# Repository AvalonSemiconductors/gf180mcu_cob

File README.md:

# gf180mcu_cob
Experimenting with Chip On Board setups for GF180MCU chips, most importantly gf180 Caravel.

Currently contains Pad-out diagrams and KiCad footprints for various GF180 dies. The KiCad footprint library also contains templates (labeled "TEMPLATE_*") which only contain Comment layer drawings showing pad locations of a specific die (pad sizes not to scale).

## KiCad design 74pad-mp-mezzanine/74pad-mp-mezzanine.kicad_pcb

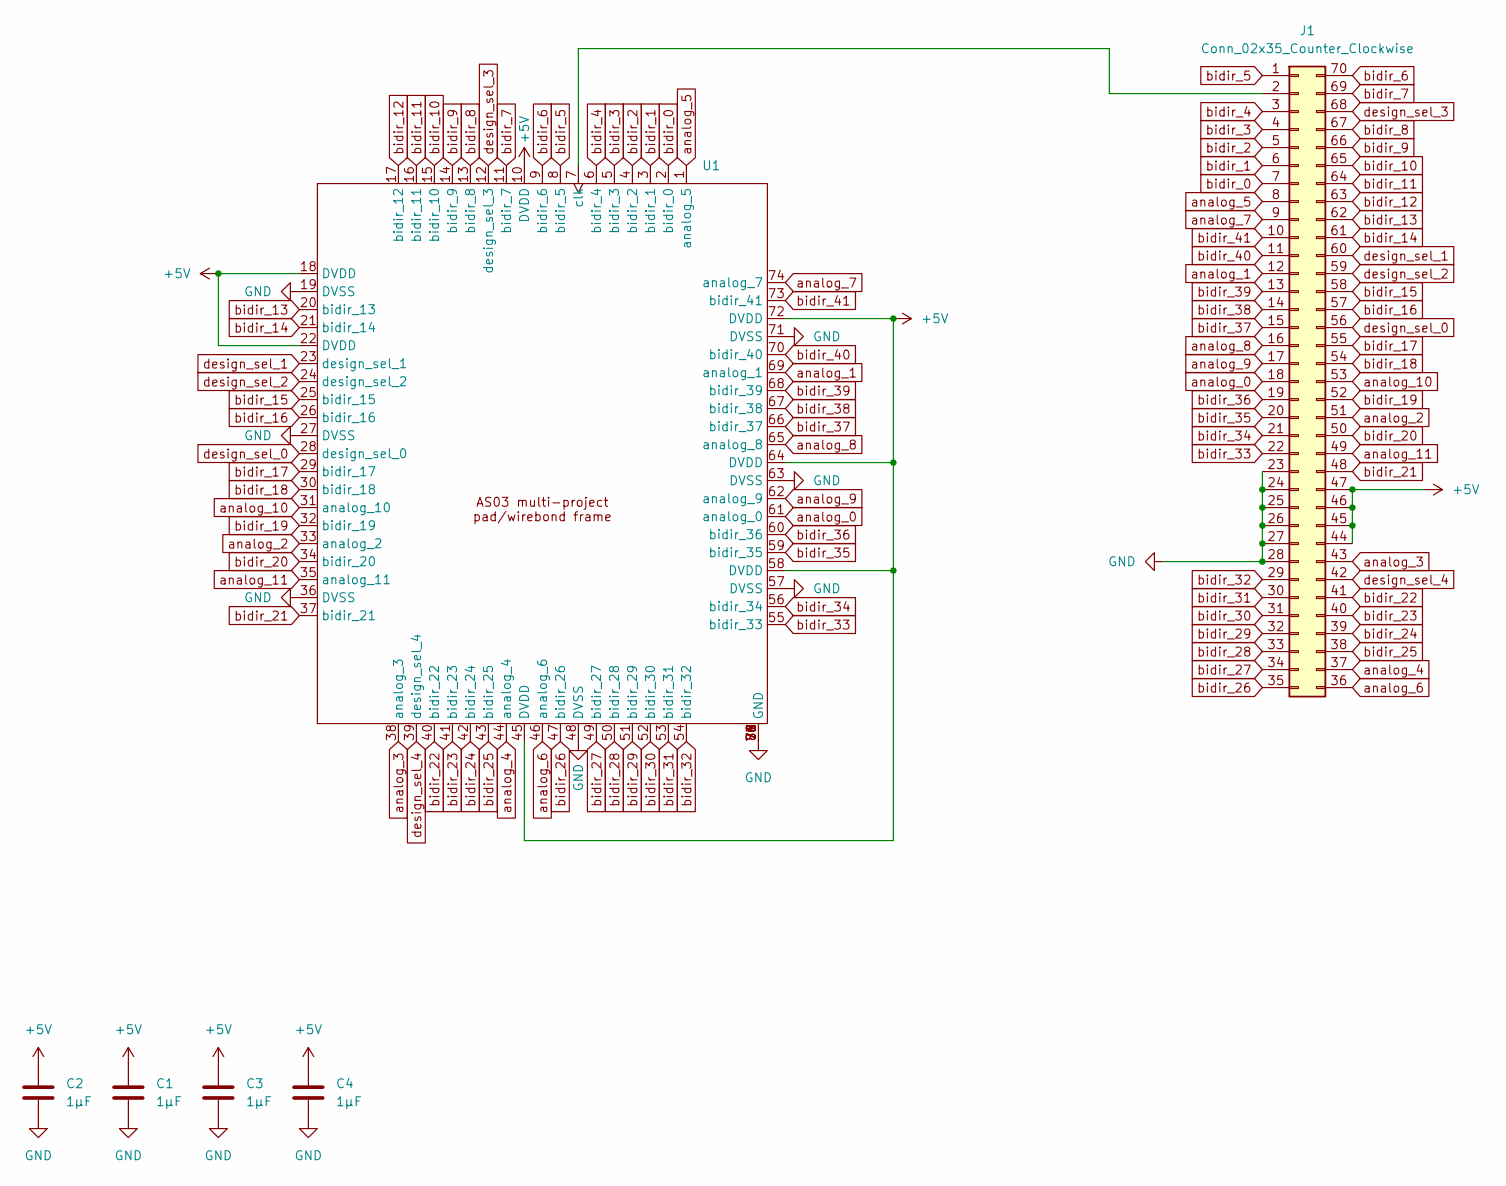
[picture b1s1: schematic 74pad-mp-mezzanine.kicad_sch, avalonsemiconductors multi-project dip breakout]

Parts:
C1, C2, C3, C4: 1µF; C_0603_1608Metric_Pad1.08x0.95mm_HandSolder
J1: Conn_02x35_Counter_Clockwise; CONN-SMD_70P-P0.40_HCTL_HC-PBB40C-70DP-0.4V-02
U1: waferspace_default_padring_v0.2

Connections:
+5V: C1.2, C2.2, C3.2, C4.2, J1.44, J1.45, J1.46, J1.47, U1.10 (DVDD), U1.18 (DVDD), U1.22 (DVDD), U1.45 (DVDD), U1.58 (DVDD), U1.64 (DVDD), U1.72 (DVDD)
GND: C1.1, C2.1, C3.1, C4.1, J1.23, J1.24, J1.25, J1.26, J1.27, J1.28, U1.19 (DVSS), U1.27 (DVSS), U1.36 (DVSS), U1.48 (DVSS), U1.57 (DVSS), U1.63 (DVSS), U1.71 (DVSS), U1.75 (GND), U1.76 (GND), U1.77 (GND), U1.78 (GND), U1.79 (GND), U1.80 (GND), U1.81 (GND)
unnamed: J1.2, U1.7 (clk)
analog_0: J1.18, U1.61 (analog_0)
analog_1: J1.12, U1.69 (analog_1)
analog_2: J1.51, U1.33 (analog_2)
analog_3: J1.43, U1.38 (analog_3)
analog_4: J1.37, U1.44 (analog_4)
analog_5: J1.8, U1.1 (analog_5)
analog_6: J1.36, U1.46 (analog_6)
analog_7: J1.9, U1.74 (analog_7)
analog_8: J1.16, U1.65 (analog_8)
analog_9: J1.17, U1.62 (analog_9)
analog_10: J1.53, U1.31 (analog_10)
analog_11: J1.49, U1.35 (analog_11)
bidir_0: J1.7, U1.2 (bidir_0)
bidir_1: J1.6, U1.3 (bidir_1)
bidir_2: J1.5, U1.4 (bidir_2)
bidir_3: J1.4, U1.5 (bidir_3)
bidir_4: J1.3, U1.6 (bidir_4)
bidir_5: J1.1, U1.8 (bidir_5)
bidir_6: J1.70, U1.9 (bidir_6)
bidir_7: J1.69, U1.11 (bidir_7)
bidir_8: J1.67, U1.13 (bidir_8)
bidir_9: J1.66, U1.14 (bidir_9)
bidir_10: J1.65, U1.15 (bidir_10)
bidir_11: J1.64, U1.16 (bidir_11)
bidir_12: J1.63, U1.17 (bidir_12)
bidir_13: J1.62, U1.20 (bidir_13)
bidir_14: J1.61, U1.21 (bidir_14)
bidir_15: J1.58, U1.25 (bidir_15)
bidir_16: J1.57, U1.26 (bidir_16)
bidir_17: J1.55, U1.29 (bidir_17)
bidir_18: J1.54, U1.30 (bidir_18)
bidir_19: J1.52, U1.32 (bidir_19)
bidir_20: J1.50, U1.34 (bidir_20)
bidir_21: J1.48, U1.37 (bidir_21)
bidir_22: J1.41, U1.40 (bidir_22)
bidir_23: J1.40, U1.41 (bidir_23)
bidir_24: J1.39, U1.42 (bidir_24)
bidir_25: J1.38, U1.43 (bidir_25)
bidir_26: J1.35, U1.47 (bidir_26)
bidir_27: J1.34, U1.49 (bidir_27)
bidir_28: J1.33, U1.50 (bidir_28)
bidir_29: J1.32, U1.51 (bidir_29)
bidir_30: J1.31, U1.52 (bidir_30)
bidir_31: J1.30, U1.53 (bidir_31)
bidir_32: J1.29, U1.54 (bidir_32)
bidir_33: J1.22, U1.55 (bidir_33)
bidir_34: J1.21, U1.56 (bidir_34)
bidir_35: J1.20, U1.59 (bidir_35)
bidir_36: J1.19, U1.60 (bidir_36)
bidir_37: J1.15, U1.66 (bidir_37)
bidir_38: J1.14, U1.67 (bidir_38)
bidir_39: J1.13, U1.68 (bidir_39)
bidir_40: J1.11, U1.70 (bidir_40)
bidir_41: J1.10, U1.73 (bidir_41)
design_sel_0: J1.56, U1.28 (design_sel_0)
design_sel_1: J1.60, U1.23 (design_sel_1)
design_sel_2: J1.59, U1.24 (design_sel_2)
design_sel_3: J1.68, U1.12 (design_sel_3)
design_sel_4: J1.42, U1.39 (design_sel_4)

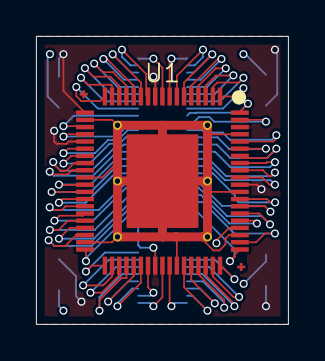
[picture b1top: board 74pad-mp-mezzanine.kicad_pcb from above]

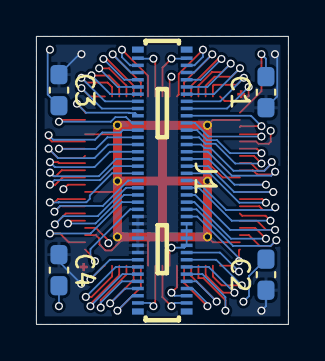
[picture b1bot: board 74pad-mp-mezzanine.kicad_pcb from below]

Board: 4 copper layers, 14.0 x 16.0 mm, 6 parts (5 on the bottom side), 62 nets.

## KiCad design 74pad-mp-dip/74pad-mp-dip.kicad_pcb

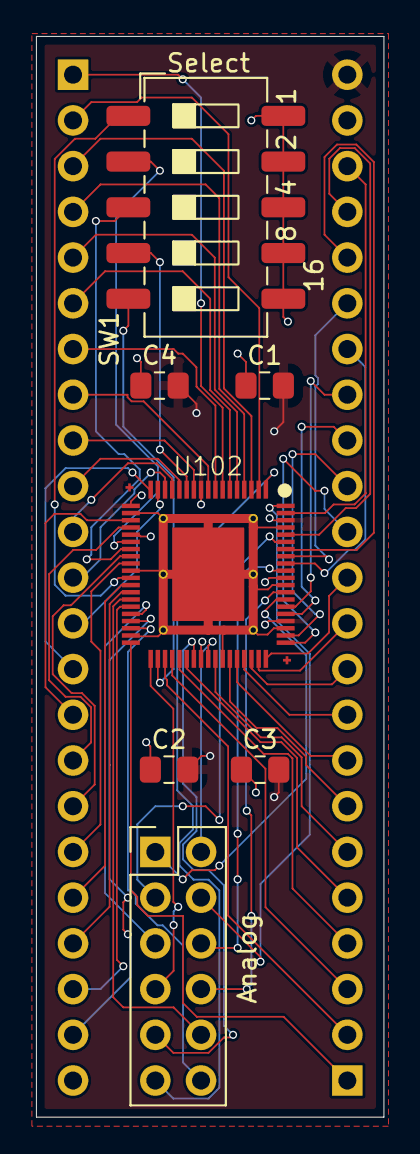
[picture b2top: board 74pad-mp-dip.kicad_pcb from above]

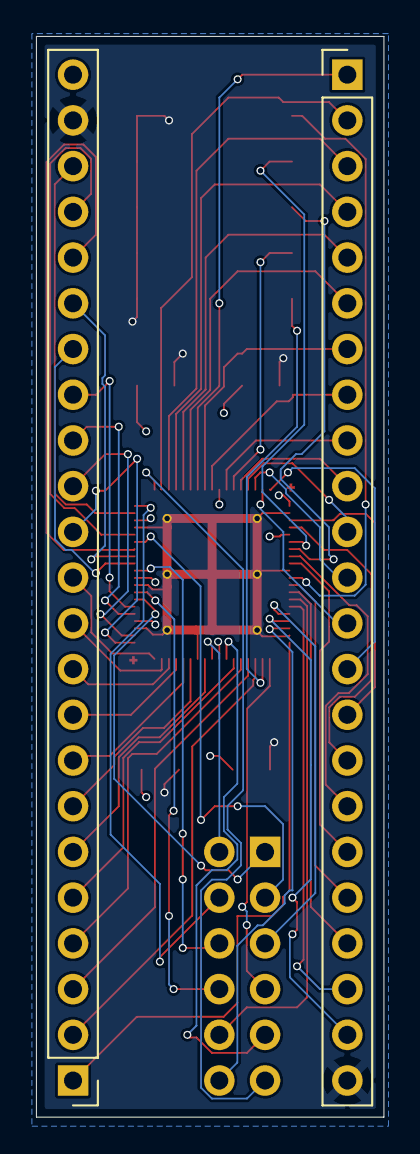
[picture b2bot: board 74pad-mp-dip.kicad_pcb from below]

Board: 4 copper layers, 19.3 x 60.0 mm, 9 parts (2 on the bottom side), 62 nets.

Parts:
C1, C2, C3, C4: 1µF; C_0805_2012Metric_Pad1.18x1.45mm_HandSolder
J1, J2: Conn_01x23_Pin; PinHeader_1x23_P2.54mm_Vertical
J3: Analog Outputs; PinHeader_2x06_P2.54mm_Vertical
SW1: SW_DIP_x05; SW_DIP_SPSTx05_Slide_6.7x14.26mm_W8.61mm_P2.54mm_LowProfile
U102: waferspace_default_padring_v0.2

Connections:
+5V: C1.2, C2.2, C3.2, C4.2, J2.23, U102.10 (DVDD), U102.18 (DVDD), U102.22 (DVDD), U102.45 (DVDD), U102.58 (DVDD), U102.64 (DVDD), U102.72 (DVDD)
GND: C1.1, C2.1, C3.1, C4.1, J1.23, J2.22, SW1.6, SW1.7, SW1.8, SW1.9, SW1.10, U102.19 (DVSS), U102.27 (DVSS), U102.36 (DVSS), U102.48 (DVSS), U102.57 (DVSS), U102.63 (DVSS), U102.71 (DVSS), U102.75 (GND), U102.76 (GND), U102.77 (GND), U102.78 (GND), U102.79 (GND), U102.80 (GND), U102.81 (GND)
unnamed: J1.1, U102.7 (clk)
analog_0: J3.1, U102.61 (analog_0)
analog_1: J3.3, U102.69 (analog_1)
analog_2: J3.5, U102.33 (analog_2)
analog_3: J3.7, U102.38 (analog_3)
analog_4: J3.9, U102.44 (analog_4)
analog_5: J3.11, U102.1 (analog_5)
analog_6: J3.2, U102.46 (analog_6)
analog_7: J3.4, U102.74 (analog_7)
analog_8: J3.6, U102.65 (analog_8)
analog_9: J3.8, U102.62 (analog_9)
analog_10: J3.10, U102.31 (analog_10)
analog_11: J3.12, U102.35 (analog_11)
bidir_0: J1.2, U102.2 (bidir_0)
bidir_1: J1.3, U102.3 (bidir_1)
bidir_2: J1.4, U102.4 (bidir_2)
bidir_3: J1.5, U102.5 (bidir_3)
bidir_4: J1.6, U102.6 (bidir_4)
bidir_5: J1.7, U102.8 (bidir_5)
bidir_6: J1.8, U102.9 (bidir_6)
bidir_7: J1.9, U102.11 (bidir_7)
bidir_8: J1.10, U102.13 (bidir_8)
bidir_9: J1.11, U102.14 (bidir_9)
bidir_10: J1.12, U102.15 (bidir_10)
bidir_11: J1.13, U102.16 (bidir_11)
bidir_12: J1.14, U102.17 (bidir_12)
bidir_13: J1.15, U102.20 (bidir_13)
bidir_14: J1.16, U102.21 (bidir_14)
bidir_15: J1.17, U102.25 (bidir_15)
bidir_16: J1.18, U102.26 (bidir_16)
bidir_17: J1.19, U102.29 (bidir_17)
bidir_18: J1.20, U102.30 (bidir_18)
bidir_19: J1.21, U102.32 (bidir_19)
bidir_20: J1.22, U102.34 (bidir_20)
bidir_21: J2.1, U102.37 (bidir_21)
bidir_22: J2.2, U102.40 (bidir_22)
bidir_23: J2.3, U102.41 (bidir_23)
bidir_24: J2.4, U102.42 (bidir_24)
bidir_25: J2.5, U102.43 (bidir_25)
bidir_26: J2.6, U102.47 (bidir_26)
bidir_27: J2.7, U102.49 (bidir_27)
bidir_28: J2.8, U102.50 (bidir_28)
bidir_29: J2.9, U102.51 (bidir_29)
bidir_30: J2.10, U102.52 (bidir_30)
bidir_31: J2.11, U102.53 (bidir_31)
bidir_32: J2.12, U102.54 (bidir_32)
bidir_33: J2.13, U102.55 (bidir_33)
bidir_34: J2.14, U102.56 (bidir_34)
bidir_35: J2.15, U102.59 (bidir_35)
bidir_36: J2.16, U102.60 (bidir_36)
bidir_37: J2.17, U102.66 (bidir_37)
bidir_38: J2.18, U102.67 (bidir_38)
bidir_39: J2.19, U102.68 (bidir_39)
bidir_40: J2.20, U102.70 (bidir_40)
bidir_41: J2.21, U102.73 (bidir_41)
design_sel_0: SW1.1, U102.28 (design_sel_0)
design_sel_1: SW1.2, U102.23 (design_sel_1)
design_sel_2: SW1.3, U102.24 (design_sel_2)
design_sel_3: SW1.4, U102.12 (design_sel_3)
design_sel_4: SW1.5, U102.39 (design_sel_4)

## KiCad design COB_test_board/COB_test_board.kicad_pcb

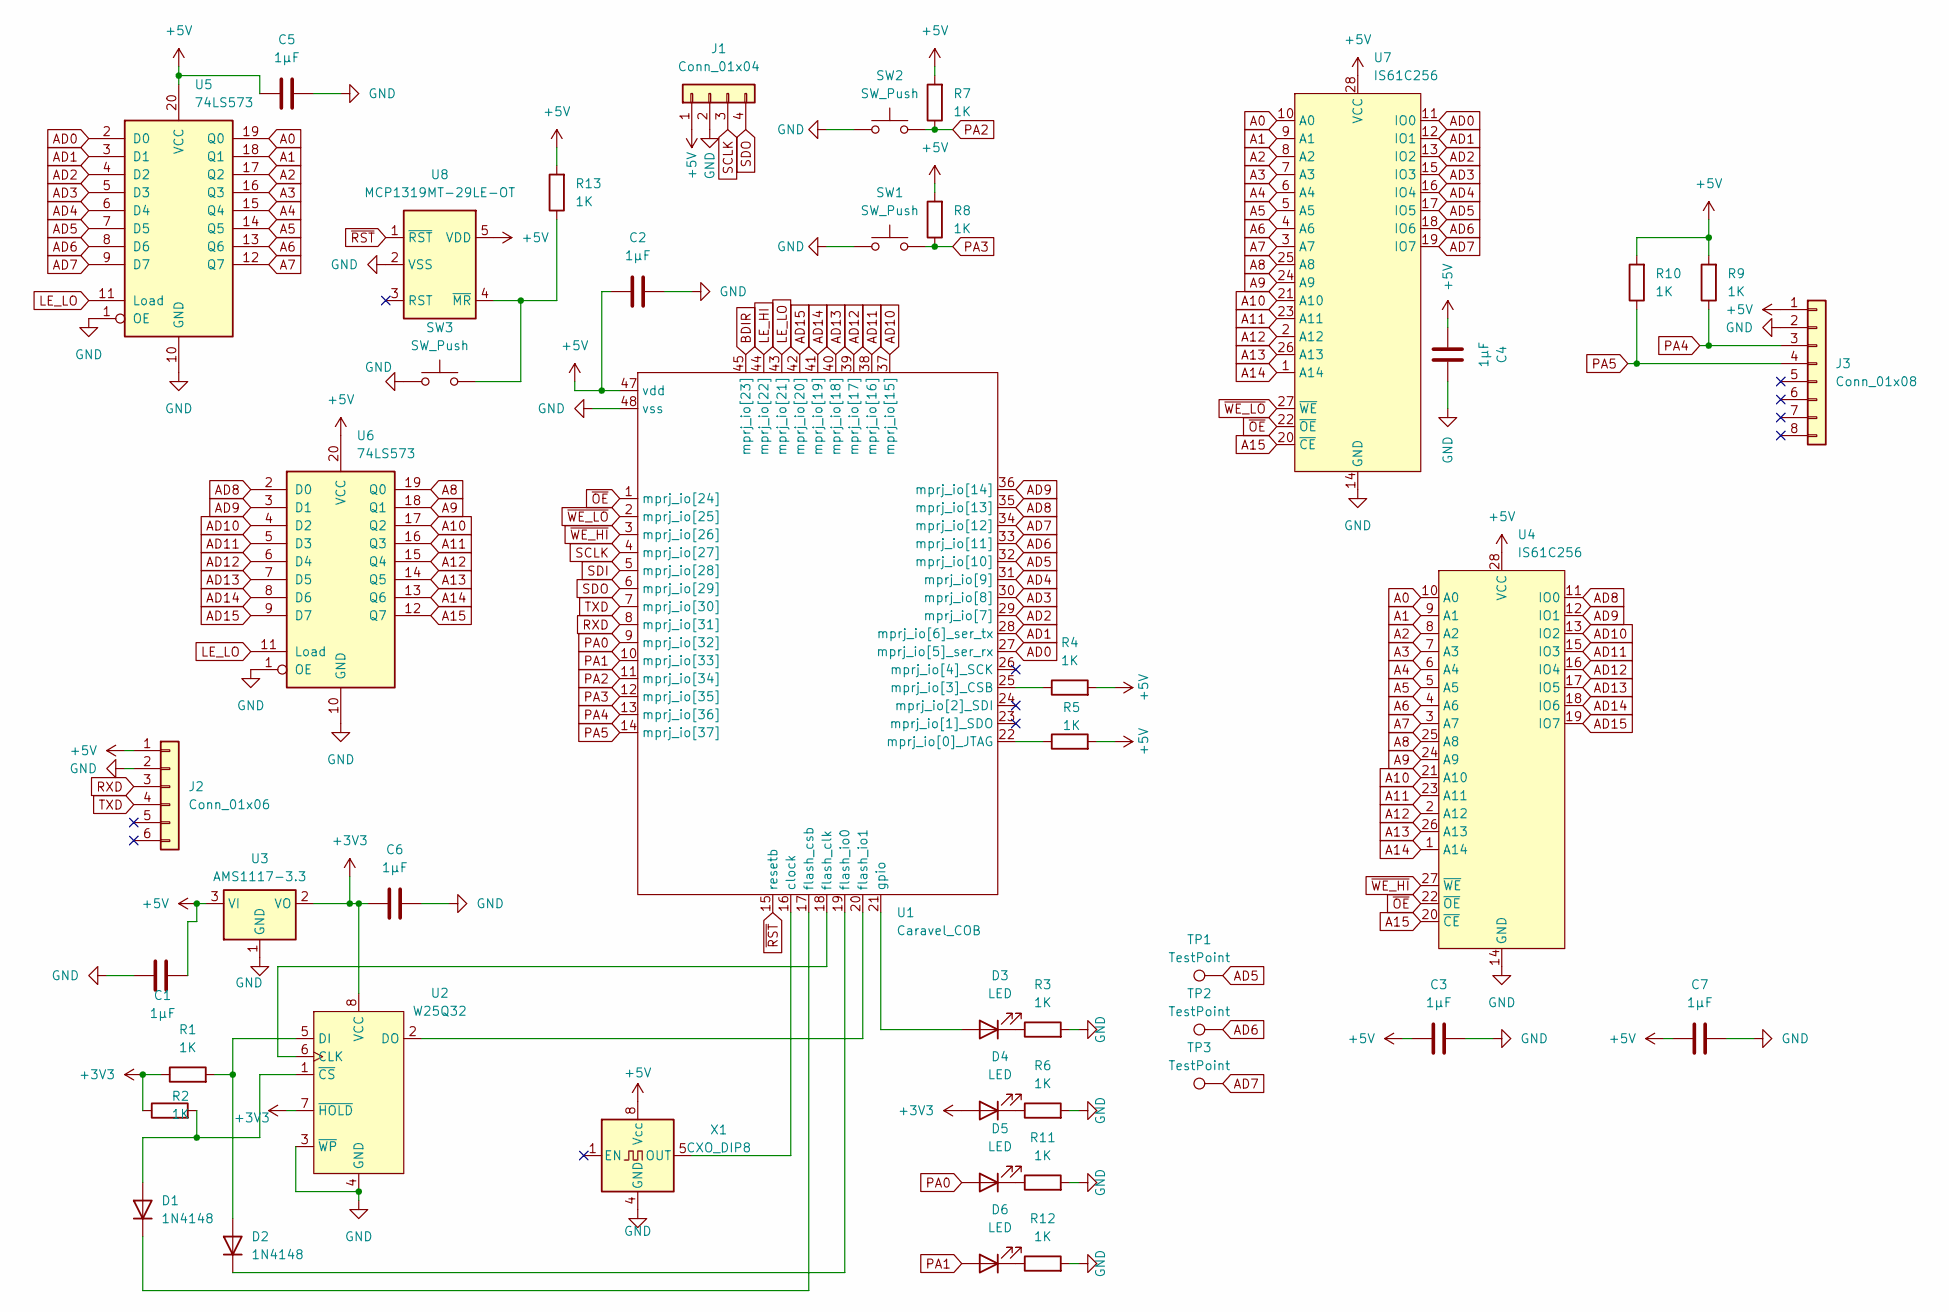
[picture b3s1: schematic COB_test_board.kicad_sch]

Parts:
C1, C2, C3, C4, C5, C6, C7: 1µF; C_0805_2012Metric_Pad1.18x1.45mm_HandSolder
D1, D2: 1N4148; D_DO-35_SOD27_P7.62mm_Horizontal
D3, D4, D5, D6: LED; LED_D3.0mm
J1: Conn_01x04; PinHeader_1x04_P2.54mm_Vertical
J2: Conn_01x06; PinSocket_1x06_P2.54mm_Vertical
J3: Conn_01x08; PinHeader_1x08_P2.54mm_Vertical
R1, R2, R3, R4, R5, R6, R7, R8, R9, R10, R11, R12, R13: 1K; R_1206_3216Metric_Pad1.30x1.75mm_HandSolder
SW1, SW2, SW3: SW_Push; SW_PUSH_6mm
TP1, TP2, TP3: TestPoint; TestPoint_Loop_D1.80mm_Drill1.0mm_Beaded
U1: Caravel_COB; caravel_gfmpw_1_0_asap
U2: W25Q32; DIP-8_W7.62mm_Socket
U3: AMS1117-3.3; SOT-223-3_TabPin2
U4, U7: IS61C256; DIP-28_W7.62mm
U5, U6: 74LS573; DIP-20_W7.62mm
U8: MCP1319MT-29LE-OT; SOT-23-5_HandSoldering
X1: CXO_DIP8; Oscillator_DIP-8

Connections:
+3V3: C6.1, D4.2 (A), R1.1, R2.1, U2.7 (~HOLD), U2.8 (VCC), U3.2 (VO)
+5V: C1.2, C2.1, C3.1, C4.1, C5.1, C7.1, J1.1, J2.1, J3.1, R4.2, R5.2, R7.2, R8.2, R9.2, R10.2, R13.2, U1.47 (vdd), U3.3 (VI), U4.28 (VCC), U5.20 (VCC), U6.20 (VCC), U7.28 (VCC), U8.5 (VDD), X1.8 (Vcc)
A0: U4.10 (A0), U5.19 (Q0), U7.10 (A0)
A1: U4.9 (A1), U5.18 (Q1), U7.9 (A1)
A2: U4.8 (A2), U5.17 (Q2), U7.8 (A2)
A3: U4.7 (A3), U5.16 (Q3), U7.7 (A3)
A4: U4.6 (A4), U5.15 (Q4), U7.6 (A4)
A5: U4.5 (A5), U5.14 (Q5), U7.5 (A5)
A6: U4.4 (A6), U5.13 (Q6), U7.4 (A6)
A7: U4.3 (A7), U5.12 (Q7), U7.3 (A7)
A8: U4.25 (A8), U6.19 (Q0), U7.25 (A8)
A9: U4.24 (A9), U6.18 (Q1), U7.24 (A9)
A10: U4.21 (A10), U6.17 (Q2), U7.21 (A10)
A11: U4.23 (A11), U6.16 (Q3), U7.23 (A11)
A12: U4.2 (A12), U6.15 (Q4), U7.2 (A12)
A13: U4.26 (A13), U6.14 (Q5), U7.26 (A13)
A14: U4.1 (A14), U6.13 (Q6), U7.1 (A14)
A15: U4.20 (~CE), U6.12 (Q7), U7.20 (~CE)
AD0: U1.27 (mprj_io[5]_ser_rx), U5.2 (D0), U7.11 (IO0)
AD1: U1.28 (mprj_io[6]_ser_tx), U5.3 (D1), U7.12 (IO1)
AD2: U1.29 (mprj_io[7]), U5.4 (D2), U7.13 (IO2)
AD3: U1.30 (mprj_io[8]), U5.5 (D3), U7.15 (IO3)
AD4: U1.31 (mprj_io[9]), U5.6 (D4), U7.16 (IO4)
AD5: TP1.1, U1.32 (mprj_io[10]), U5.7 (D5), U7.17 (IO5)
AD6: TP2.1, U1.33 (mprj_io[11]), U5.8 (D6), U7.18 (IO6)
AD7: TP3.1, U1.34 (mprj_io[12]), U5.9 (D7), U7.19 (IO7)
AD8: U1.35 (mprj_io[13]), U4.11 (IO0), U6.2 (D0)
AD9: U1.36 (mprj_io[14]), U4.12 (IO1), U6.3 (D1)
AD10: U1.37 (mprj_io[15]), U4.13 (IO2), U6.4 (D2)
AD11: U1.38 (mprj_io[16]), U4.15 (IO3), U6.5 (D3)
AD12: U1.39 (mprj_io[17]), U4.16 (IO4), U6.6 (D4)
AD13: U1.40 (mprj_io[18]), U4.17 (IO5), U6.7 (D5)
AD14: U1.41 (mprj_io[19]), U4.18 (IO6), U6.8 (D6)
AD15: U1.42 (mprj_io[20]), U4.19 (IO7), U6.9 (D7)
BDIR: U1.45 (mprj_io[23])
GND: C1.1, C2.2, C3.2, C4.2, C5.2, C6.2, C7.2, J1.2, J2.2, J3.2, R3.2, R6.2, R11.2, R12.2, SW1.1, SW2.1, SW3.1, U1.48 (vss), U2.3 (~WP), U2.4 (GND), U3.1 (GND), U4.14 (GND), U5.1 (OE), U5.10 (GND), U6.1 (OE), U6.10 (GND), U7.14 (GND), U8.2 (VSS), X1.4 (GND)
LE_HI: U1.44 (mprj_io[22])
LE_LO: U1.43 (mprj_io[21]), U5.11 (Load), U6.11 (Load)
unnamed: D1.2 (A), R2.2, U2.1 (~CS)
unnamed: D1.1 (K), U1.17 (flash_csb)
unnamed: D2.2 (A), R1.2, U2.5 (DI)
unnamed: D2.1 (K), U1.19 (flash_io0)
unnamed: D3.2 (A), U1.21 (gpio)
unnamed: D3.1 (K), R3.1
unnamed: D4.1 (K), R6.1
unnamed: D5.1 (K), R11.1
unnamed: D6.1 (K), R12.1
unnamed: U1.16 (clock), X1.5 (OUT)
unnamed: U1.18 (flash_clk), U2.6 (CLK)
unnamed: U1.20 (flash_io1), U2.2 (DO)
unnamed: R5.1, U1.22 (mprj_io[0]_JTAG)
unnamed: R4.1, U1.25 (mprj_io[3]_CSB)
unnamed: R13.1, SW3.2, U8.4 (~MR)
PA0: D5.2 (A), U1.9 (mprj_io[32])
PA1: D6.2 (A), U1.10 (mprj_io[33])
PA2: R7.1, SW2.2, U1.11 (mprj_io[34])
PA3: R8.1, SW1.2, U1.12 (mprj_io[35])
PA4: J3.3, R9.1, U1.13 (mprj_io[36])
PA5: J3.4, R10.1, U1.14 (mprj_io[37])
RXD: J2.3, U1.8 (mprj_io[31])
SCLK: J1.3, U1.4 (mprj_io[27])
SDI: U1.5 (mprj_io[28])
SDO: J1.4, U1.6 (mprj_io[29])
TXD: J2.4, U1.7 (mprj_io[30])
~OE: U1.1 (mprj_io[24]), U4.22 (~OE), U7.22 (~OE)
~RST: U1.15 (resetb), U8.1 (~RST)
~WE_HI: U1.3 (mprj_io[26]), U4.27 (~WE)
~WE_LO: U1.2 (mprj_io[25]), U7.27 (~WE)

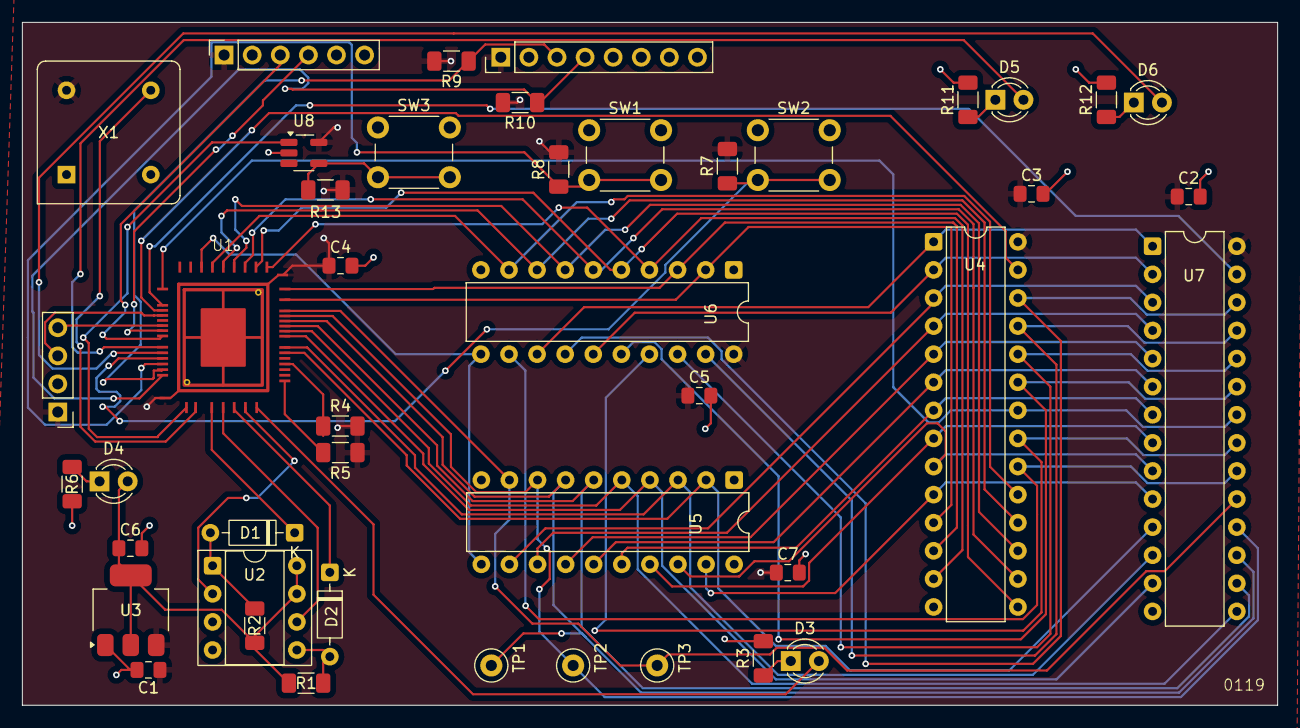
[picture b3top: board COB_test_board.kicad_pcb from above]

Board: 4 copper layers, 113.5 x 61.8 mm, 44 parts (0 on the bottom side), 65 nets.

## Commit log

2025-08-21 Initial commit.
2025-08-25 Fix caravel padout dimensions
2025-09-13 COB Test Board
2025-09-21 DIP-40 based COB footprint
2026-02-16 Multi-project die COB boards.2
2026-04-19 cob panel created
